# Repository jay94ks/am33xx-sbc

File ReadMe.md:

# AM33xx SBC project.
This project is to create a SBC (Single board computer).
However, despite its name, it is divided into several boards.

## Power-supply board.
  This take power from Type-C USB, and regulates it to 3.3v, 1.8v, 1.5v and 1.1v LDO.
and `STM32G030F6P6` controls power sequence of each voltage lines. And, unfortunately, 
current implementation has no `On/Off` button. when the power cable attached, 
this just turn the board on.

### Rendering:

### Schematic:

### Pinmap.
Pins of the mini power-supply board has following pin map (2.54mm pitch):

```
Right to left order.
1. 1v1
2. 1v5
3. 1v8
4. 3v3
5. 5v
6. SYS_EN
7. USB_DP
8. USB_DM
9. PWRONRSTn
10. WARMRSTn
11. GND
12. GND
```

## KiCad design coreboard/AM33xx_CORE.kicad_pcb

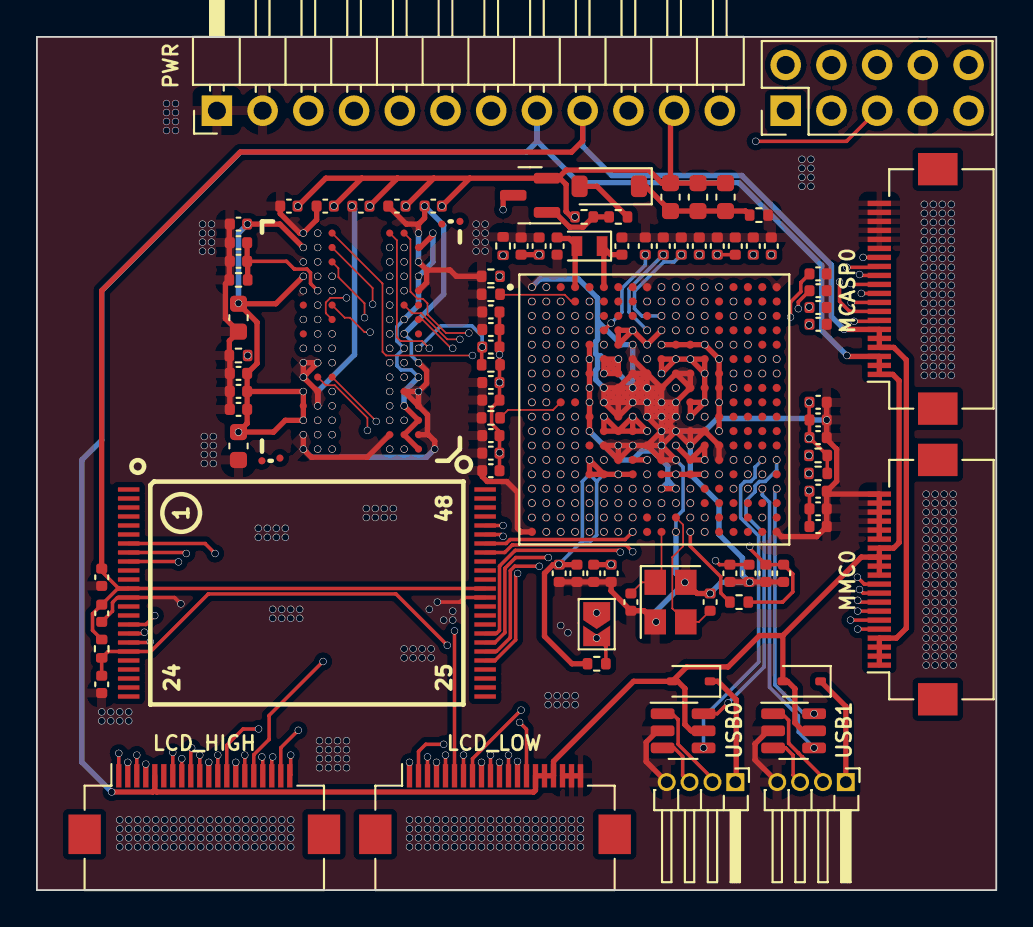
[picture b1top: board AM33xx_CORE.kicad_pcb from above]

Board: 8 copper layers, 53.3 x 47.4 mm, 94 parts (0 on the bottom side), 154 nets.

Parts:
C1, C2, C3, C4, C5, C6, C7, C8, C11, C12, C13, C14, C16, C17, C18, C19, C20, C21, C22, C23, C24, C25, C26, C27, C28, C29, C30, C31, C32, C33, C34, C35, C45, C46, C47, C48, C49, C50, C51, C52, C53, C54, C55, C56, C57, C58: 100nF; C_0402_1005Metric
C9, C10, C59, C60: 10uF; C_0603_1608Metric
C15: 2.2uF; C_0603_1608Metric
C36, C38, C40, C42: 1uF; C_0402_1005Metric
C39, C41: 6.8pF; C_0402_1005Metric
C43, C44: 28pF; C_0402_1005Metric
D1, D3: 1N5819WS; D_SOD-323
D2: 1N4148W; D_SOD-123
J1: PWR; PinHeader_1x12_P2.54mm_Horizontal
J2, J3: Conn_01x04; PinHeader_1x04_P1.27mm_Horizontal
J6: JTAG; PinHeader_2x05_P2.54mm_Vertical
J7: MMC0; Hirose_FH12-20S-0.5SH_1x20-1MP_P0.50mm_Horizontal
J8: LCD_HIGH; Hirose_FH12-20S-0.5SH_1x20-1MP_P0.50mm_Horizontal
J9: LCD_LOW; Hirose_FH12-20S-0.5SH_1x20-1MP_P0.50mm_Horizontal
J10: MCASP0_FPC; Hirose_FH12-20S-0.5SH_1x20-1MP_P0.50mm_Horizontal
JP1: Jumper_2_Open; SolderJumper-2_P1.3mm_Open_TrianglePad1.0x1.5mm
Q1: MMBT3906; SOT-23
R1, R2, R5, R10, R11, R12: 10k; R_0402_1005Metric
R3, R4: 47k; R_0402_1005Metric
R6, R8: 37k; R_0402_1005Metric
R7: 4.7k; R_0402_1005Metric
R9: 47; R_0402_1005Metric
R13, R14: 2k; R_0402_1005Metric
R15: 160k; R_0402_1005Metric
U1, U2: USBLC6-2SC6; SOT-23-6
U3: AM3352BZCZ100; BGA324CP80_18X18_1500X1500X140B50N
U4: H27UBG8T2BTR-BC(TSOP48); TSOP48
U5: H5TQ2G63BFR_MEM4G16D3EABG-125--H5TC8G63AMR-PBA_K4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; FBGA96(HYNIX_SAMSUNG_512MX16_DDR3)
Y1: 32.768kHz; Crystal_SMD_2012-2Pin_2.0x1.2mm
Y2: 24MHz; Crystal_SMD_3225-4Pin_3.2x2.5mm

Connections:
+1.5V: C9.1, C10.1, C15.1, C20.1, C21.1, C24.1, C25.1, C28.1, C29.1, C32.1, C33.1, C48.1, C51.1, C52.1, C53.1, C54.1, C55.1, C56.1, C57.1, C58.1, C59.1, C60.1, J1.11, Q1.2 (E), R3.1, R13.1, U3.D7 (VDDS_RTC), U3.D8 (VDDA_ADC), U3.D10 (VDDS_SRAM_MPU_BB), U3.E5 (VDDS_DDR), U3.E7 (VDDS_PLL_DDR), U3.E9 (VDDS_SRAM_CORE_BG), U3.F5 (VDDS_DDR), U3.G5 (VDDS_DDR), U3.H5 (VDDS_DDR), U3.H15 (VDDS_PLL_MPU), U3.J5 (VDDS_DDR), U3.K5 (VDDS_DDR), U3.L5 (VDDS_DDR), U3.R10 (VDDS_PLL_CORE_LCD), U3.R11 (VDDS_OSC), U5.A1 (VDDQ), U5.A8 (VDDQ), U5.B2 (VDD), U5.C1 (VDDQ), U5.C9 (VDDQ), U5.D2 (VDDQ), U5.D9 (VDD), U5.E9 (VDDQ), U5.F1 (VDDQ), U5.G7 (VDD), U5.H2 (VDDQ), U5.H9 (VDDQ), U5.K2 (VDD), U5.K8 (VDD), U5.N1 (VDD), U5.N9 (VDD), U5.R1 (VDD), U5.R9 (VDD)
+1V1: C1.1, C2.1, C5.1, C6.1, C11.1, C12.1, C16.1, C17.1, J1.12, U3.A2 (VDD_MPU_MON), U3.F6 (VDD_CORE), U3.F7 (VDD_CORE), U3.F10 (VDD_MPU), U3.F11 (VDD_MPU), U3.F12 (VDD_MPU), U3.F13 (VDD_MPU), U3.G6 (VDD_CORE), U3.G7 (VDD_CORE), U3.G10 (VDD_CORE), U3.G13 (VDD_MPU), U3.H11 (VDD_CORE), U3.H13 (VDD_MPU), U3.J12 (VDD_CORE), U3.J13 (VDD_MPU), U3.K6 (VDD_CORE), U3.K8 (VDD_CORE), U3.K12 (VDD_CORE), U3.L6 (VDD_CORE), U3.L7 (VDD_CORE), U3.L8 (VDD_CORE), U3.L9 (VDD_CORE), U3.M11 (VDD_CORE), U3.M13 (VDD_CORE), U3.N8 (VDD_CORE), U3.N9 (VDD_CORE), U3.N12 (VDD_CORE), U3.N13 (VDD_CORE)
+1V8: C3.1, C4.1, C7.1, C8.1, C13.1, C14.1, C18.1, C19.1, J1.10, U3.B9 (VREFP), U3.E6 (VDDS), U3.E14 (VDDS), U3.F9 (VDDS), U3.K13 (VDDS), U3.N6 (VDDS), U3.N16 (VDDA1P8V_USB0), U3.P9 (VDDS), U3.P14 (VDDS), U3.R16 (VDDA1P8V_USB1)
+3V3: C22.1, C23.1, C26.1, C27.1, C30.1, C31.1, C34.1, C35.1, C46.1, C47.1, J1.9, J7.1, J7.2, J7.3, J7.4, J10.4, J10.5, J10.6, R6.1, R8.1, R10.1, R11.2, R12.1, U3.E10 (VDDSHV6), U3.E11 (VDDSHV6), U3.E12 (VDDSHV6), U3.E13 (VDDSHV6), U3.F14 (VDDSHV6), U3.G14 (VDDSHV6), U3.H14 (VDDSHV4), U3.J14 (VDDSHV4), U3.K14 (VDDSHV5), U3.L14 (VDDSHV5), U3.N5 (VDDSHV6), U3.N15 (VDDA3P3V_USB0), U3.P5 (VDDSHV6), U3.P6 (VDDSHV6), U3.P7 (VDDSHV1), U3.P8 (VDDSHV1), U3.P10 (VDDSHV2), U3.P11 (VDDSHV2), U3.P12 (VDDSHV3), U3.P13 (VDDSHV3), U3.R15 (VDDA3P3V_USB1), U4.12 (VCC), U4.37 (VCC)
+5V: D1.2 (A), D3.2 (A), J1.8, J7.11, J7.12, J7.13, J7.14, J8.5, J9.15, J9.16, J9.17, J10.1, J10.2, J10.3, U1.5 (VBUS), U2.5 (VBUS)
/DDR_A0: U3.F3 (DDR_A0), U5.N3 (A0)
/DDR_A1: U3.H1 (DDR_A1), U5.P7 (A1)
/DDR_A2: U3.E4 (DDR_A2), U5.P3 (A2)
/DDR_A3: U3.C3 (DDR_A3), U5.N2 (A3)
/DDR_A4: U3.C2 (DDR_A4), U5.P8 (A4)
/DDR_A5: U3.B1 (DDR_A5), U5.P2 (A5)
/DDR_A6: U3.D5 (DDR_A6), U5.R8 (A6)
/DDR_A7: U3.E2 (DDR_A7), U5.R2 (A7)
/DDR_A8: U3.D4 (DDR_A8), U5.T8 (A8)
/DDR_A9: U3.C1 (DDR_A9), U5.R3 (A9)
/DDR_A10: U3.F4 (DDR_A10), U5.L7 (A10/AP)
/DDR_A11: U3.F2 (DDR_A11), U5.R7 (A11)
/DDR_A12: U3.E3 (DDR_A12), U5.N7 (A12/#BC)
/DDR_A13: U3.H3 (DDR_A13), U5.T3 (A13)
/DDR_A14: U3.H4 (DDR_A14), U5.T7 (NC/A14)
/DDR_A15: U3.D3 (DDR_A15), U5.M7 (NC/A15)
/DDR_BA0: U3.C4 (DDR_BA0), U5.M2 (BA0)
/DDR_BA1: U3.E1 (DDR_BA1), U5.N8 (BA1)
/DDR_BA2: U3.B3 (DDR_BA2), U5.M3 (BA2)
/DDR_CASN: U3.F1 (DDR_CASN), U5.K3 (#CAS)
/DDR_CK: U3.D2 (DDR_CK), U5.J7 (CK)
/DDR_CKE: U3.G3 (DDR_CKE), U5.K9 (CKE)
/DDR_CKN: U3.D1 (DDR_CKN), U5.K7 (#CK)
/DDR_CSN0: U3.H2 (DDR_CSN0), U5.L2 (#CS)
/DDR_D0: U3.M3 (DDR_D0), U5.E3 (DQL0)
/DDR_D1: U3.M4 (DDR_D1), U5.F7 (DQL1)
/DDR_D2: U3.N1 (DDR_D2), U5.F2 (DQL2)
/DDR_D3: U3.N2 (DDR_D3), U5.F8 (DQL3)
/DDR_D4: U3.N3 (DDR_D4), U5.H3 (DQL4)
/DDR_D5: U3.N4 (DDR_D5), U5.H8 (DQL5)
/DDR_D6: U3.P3 (DDR_D6), U5.G2 (DQL6)
/DDR_D7: U3.P4 (DDR_D7), U5.H7 (DQL7)
/DDR_D8: U3.J1 (DDR_D8), U5.D7 (DQU0)
/DDR_D9: U3.K1 (DDR_D9), U5.C3 (DQU1)
/DDR_D10: U3.K2 (DDR_D10), U5.C8 (DQU2)
/DDR_D11: U3.K3 (DDR_D11), U5.C2 (DQU3)
/DDR_D12: U3.K4 (DDR_D12), U5.A7 (DQU4)
/DDR_D13: U3.L3 (DDR_D13), U5.A2 (DQU5)
/DDR_D14: U3.L4 (DDR_D14), U5.B8 (DQU6)
/DDR_D15: U3.M1 (DDR_D15), U5.A3 (DQU7)
/DDR_DQM0: U3.M2 (DDR_DQM0), U5.E7 (DML)
/DDR_DQM1: U3.J2 (DDR_DQM1), U5.D3 (DMU)
/DDR_DQS0: U3.P1 (DDR_DQS0), U5.F3 (DQSL)
/DDR_DQS1: U3.L1 (DDR_DQS1), U5.C7 (DQSU)
/DDR_DQSN0: U3.P2 (DDR_DQSN0), U5.G3 (#DQSL)
/DDR_DQSN1: U3.L2 (DDR_DQSN1), U5.B7 (#DQSU)
/DDR_ODT: U3.G1 (DDR_ODT), U5.K1 (ODT)
/DDR_RASN: U3.G4 (DDR_RASN), U5.J3 (#RAS)
/DDR_RSTN: U3.G2 (DDR_RESETN), U5.T2 (#RESET)
/DDR_WEN: U3.B2 (DDR_WEN), U5.L3 (#WE)
/GMPC_CSN0: JP1.1 (A), U3.V6 (GPMC_CSN0)
/GPMC_AD0: U3.U7 (GPMC_AD0), U4.29 (I/O0)
/GPMC_AD1: U3.V7 (GPMC_AD1), U4.30 (I/O1)
/GPMC_AD2: U3.R8 (GPMC_AD2), U4.31 (I/O2)
/GPMC_AD3: U3.T8 (GPMC_AD3), U4.32 (I/O3)
/GPMC_AD4: U3.U8 (GPMC_AD4), U4.41 (I/O4)
/GPMC_AD5: U3.V8 (GPMC_AD5), U4.42 (I/O5)
/GPMC_AD6: U3.R9 (GPMC_AD6), U4.43 (I/O6)
/GPMC_AD7: U3.T9 (GPMC_AD7), U4.44 (I/O7)
/GPMC_ALE: U3.R7 (GPMC_ADVN_ALE), U4.17 (ALE)
/GPMC_CLE: U3.T6 (GPMC_BEN0_CLE), U4.16 (CLE)
/GPMC_CLK: R12.2, U3.V12 (GPMC_CLK), U4.7 (RB1#)
/GPMC_REN: U3.T7 (GPMC_OEN_REN), U4.8 (#RE)
/GPMC_WEN: U3.U6 (GPMC_WEN), U4.18 (#WE)
/GPMC_WPN: C45.1, R10.2, U3.U17 (GPMC_WPN), U4.19 (#WP)
/LCD_D0/R3: J8.11, U3.R1 (LCD_DATA0)
/LCD_D1/R4: J8.12, U3.R2 (LCD_DATA1)
/LCD_D2/R5: J8.14, U3.R3 (LCD_DATA2)
/LCD_D3/R6: J9.14, U3.R4 (LCD_DATA3)
/LCD_D4/R7: J8.13, U3.T1 (LCD_DATA4)
/LCD_D5/G2: J8.17, U3.T2 (LCD_DATA5)
/LCD_D6/G3: J8.20, U3.T3 (LCD_DATA6)
/LCD_D7/G4: J9.1, U3.T4 (LCD_DATA7)
/LCD_D8/G5: J9.2, U3.U1 (LCD_DATA8)
/LCD_D9/G6: J8.18, U3.U2 (LCD_DATA9)
/LCD_D10/G7: J8.19, U3.U3 (LCD_DATA10)
/LCD_D11/B3: J9.8, U3.U4 (LCD_DATA11)
/LCD_D12/B4: J9.9, U3.V2 (LCD_DATA12)
/LCD_D13/B5: J9.10, U3.V3 (LCD_DATA13)
/LCD_D14/B6: J9.4, U3.V4 (LCD_DATA14)
/LCD_D15/B7: J9.5, U3.T5 (LCD_DATA15)
/LCD_D16/R2: J8.10, U3.U13 (GPMC_AD15)
/LCD_D17/B2: J9.7, U3.V13 (GPMC_AD14)
/LCD_D18/R1: J8.9, U3.R12 (GPMC_AD13)
/LCD_D19/G1: J8.16, U3.T12 (GPMC_AD12)
/LCD_D20/B1: J9.6, U3.U12 (GPMC_AD11)
/LCD_D21/R0: J8.8, U3.T11 (GPMC_AD10)
/LCD_D22/G0: J8.15, U3.T10 (GPMC_AD9)
/LCD_D23/B0: J9.3, U3.U10 (GPMC_AD8)
/LCD_D24/HSYNC: J9.11, U3.R5 (LCD_HSYNC)
/LCD_D25/VSYNC: J9.12, U3.U5 (LCD_VSYNC)
/LCD_D26/ENABLE: J9.13, U3.R6 (LCD_AC_BIAS_EN)
/LCD_D27/PCLK: J8.7, U3.V5 (LCD_PCLK)
/USB_RAW_DM0: J2.2, U1.1 (I/O1)
/USB_RAW_DM1: J3.2, U2.1 (I/O1)
/USB_RAW_DP0: J2.3, U1.3 (I/O2)
/USB_RAW_DP1: J3.3, U2.3 (I/O2)
EDID_SCL: J8.3, U3.C16 (I2C0_SCL)
EDID_SDA: J8.4, U3.C17 (I2C0_SDA)
GND: C1.2, C2.2, C3.2, C4.2, C5.2, C6.2, C7.2, C8.2, C11.2, C12.2, C13.2, C14.2, C16.2, C17.2, C18.2, C19.2, C20.2, C21.2, C22.2, C23.2, C24.2, C25.2, C26.2, C27.2, C28.2, C29.2, C30.2, C31.2, C32.2, C33.2, C34.2, C35.2, C36.2, C38.2, C39.1, C40.2, C41.1, C42.2, C43.1, C44.1, C45.2, C46.2, C47.2, C49.2, C50.2, C51.2, C52.2, C53.2, C54.2, C55.2, C56.2, C57.2, C58.2, C59.2, C60.2, J1.1, J1.2, J2.4, J3.4, J6.7, J6.8, J7.15, J7.16, J7.17, J7.18, J7.19, J7.20, J8.6, J9.18, J9.19, J9.20, J10.15, J10.16, J10.17, J10.18, J10.19, J10.20, R1.2, R4.2, R5.2, R7.2, R9.1, R14.2, R15.2, U1.2 (GND), U2.2 (GND), U3.A1 (VSS), U3.A5 (VSS_RTC), U3.A9 (VREFN), U3.A18 (VSS), U3.E8 (VSSA_ADC), U3.F8 (VSS), U3.G8 (VSS), U3.G9 (VSS), U3.G11 (VSS), U3.G12 (VSS), U3.H6 (VSS), U3.H7 (VSS), U3.H8 (VSS), U3.H9 (VSS), U3.H10 (VSS), U3.H12 (VSS), U3.J6 (VSS), U3.J7 (VSS), U3.J8 (VSS), U3.J9 (VSS), U3.J10 (VSS), U3.J11 (VSS), U3.K7 (VSS), U3.K9 (VSS), U3.K10 (VSS), U3.K11 (VSS), U3.L10 (VSS), U3.L11 (VSS), U3.L12 (VSS), U3.L13 (VSS), U3.M6 (VSS), U3.M7 (VSS), U3.M8 (VSS), U3.M9 (VSS), U3.M10 (VSS), U3.M12 (VSS), U3.M14 (VSSA_USB), U3.N7 (VSS), U3.N10 (VSS), U3.N11 (VSS), U3.N14 (VSSA_USB), U3.V1 (VSS), U3.V11 (VSS_OSC), U3.V18 (VSS), U4.13 (VSS), U4.36 (VSS), U5.A9 (VSS), U5.B1 (VSSQ), U5.B3 (VSS), U5.B9 (VSSQ), U5.D1 (VSSQ), U5.D8 (VSSQ), U5.E1 (VSS), U5.E2 (VSSQ), U5.E8 (VSSQ), U5.F9 (VSSQ), U5.G1 (VSSQ), U5.G8 (VSS), U5.G9 (VSSQ), U5.J2 (VSS), U5.J8 (VSS), U5.M1 (VSS), U5.M9 (VSS), U5.P1 (VSS), U5.P9 (VSS), U5.T1 (VSS), U5.T9 (VSS), Y2.2, Y2.4
MCASP0_ACLKR: J10.8, U3.B12 (MCASP0_ACLKR)
MCASP0_ACLKX: J10.11, U3.A13 (MCASP0_ACLKX)
MCASP0_AHCLKR: J10.9, U3.C12 (MCASP0_AHCLKR)
MCASP0_AHCLKX: J10.10, U3.A14 (MCASP0_AHCLKX)
MCASP0_AXR0: J10.13, U3.D12 (MCASP0_AXR0)
MCASP0_AXR1: J10.14, U3.D13 (MCASP0_AXR1)
MCASP0_FSR: J10.12, U3.C13 (MCASP0_FSR)
MCASP0_FSX: J10.7, U3.B13 (MCASP0_FSX)
MMC0_CLK: J7.6, U3.G17 (MMC0_CLK)
MMC0_CMD: J7.5, U3.G18 (MMC0_CMD)
MMC0_DAT0: J7.7, U3.G16 (MMC0_DAT0)
MMC0_DAT1: J7.8, U3.G15 (MMC0_DAT1)
MMC0_DAT2: J7.9, U3.F18 (MMC0_DAT2)
MMC0_DAT3: J7.10, U3.F17 (MMC0_DAT3)
unnamed: D1.1 (K), J2.1
unnamed: D2.2 (A), R2.1
unnamed: C9.2, C10.2, C15.2, D2.1 (K), R1.1
unnamed: D3.1 (K), J3.1
unnamed: JP1.2 (B), R11.1, U4.9 (CE1#)
unnamed: Q1.1 (B), R2.2, R3.2
unnamed: C36.1, U3.C10 (CAP_VBB_MPU)
unnamed: C42.1, U3.D6 (CAP_VDD_RTC)
unnamed: C40.1, U3.D9 (CAP_VDD_SRAM_CORE)
unnamed: C38.1, U3.D11 (CAP_VDD_SRAM_MPU)
unnamed: R9.2, U3.J3 (DDR_VTP)
unnamed: R7.1, U3.C5 (EXT_WAKEUP)
unnamed: R5.1, U3.B4 (RTC_KALDO_ENN)
unnamed: C41.2, U3.A4 (RTC_XTALOUT), Y1.2
unnamed: R8.2, U3.P16 (USB0_ID)
unnamed: R6.2, U3.P17 (USB1_ID)
unnamed: C44.2, U3.U11 (XTALOUT), Y2.3
unnamed: C48.2, C49.1, C50.1, R13.2, R14.1, U5.H1 (VREFDQ), U5.M8 (VREFCA)
unnamed: R15.1, U5.L8 (ZQ)
PWR_PWRONRSTn: J1.4, U3.B15 (PWRONRSTN)
PWR_WARMRSTn: J1.3, U3.A10 (WARMRSTN)
RTC_PORZ: Q1.3 (C), R4.1, U3.B5 (RTC_PWRONRSTN)
RTC_XTAL_IN: C39.2, U3.A6 (RTC_XTALIN), Y1.1
TCK: J6.4, U3.A12 (TCK)
TDI: J6.2, U3.B11 (TDI)
TDO: J6.1, U3.A11 (TDO)
TMS: J6.3, U3.C11 (TMS)
TRST: J6.5, U3.B10 (~TRSTN)
UART0_RXD: J8.1, U3.E15 (UART0_RXD)
UART0_TXD: J8.2, U3.E16 (UART0_TXD)
USB0_DM: U1.6 (I/O1), U3.N18 (USB0_DM)
USB0_DP: U1.4 (I/O2), U3.N17 (USB0_DP)
USB1_DM: U2.6 (I/O1), U3.R18 (USB1_DM)
USB1_DP: U2.4 (I/O2), U3.R17 (USB1_DP)
XTAL_IN: C43.2, U3.V10 (XTALIN), Y2.1

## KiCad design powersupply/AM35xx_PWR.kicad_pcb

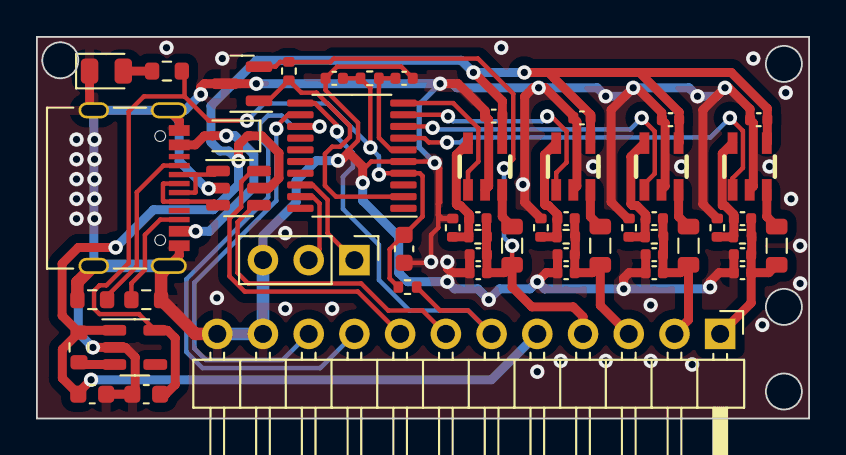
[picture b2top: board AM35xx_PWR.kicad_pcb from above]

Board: 2 copper layers, 42.9 x 21.2 mm, 53 parts (0 on the bottom side), 35 nets.

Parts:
C2, C3, C6, C7, C8, C9, C10, C11, C15, C16, C17, C18: 22uF; C_0402_1005Metric
C4, C5, C12, C13: 22pF; C_0402_1005Metric
C14, C19: 10uF; C_0603_1608Metric
C20, C21: 100nF; C_0402_1005Metric
C22: 4.7uF; C_0603_1608Metric
D1: 1N5819WS; D_SOD-323
D2: LED/G; LED_0805_2012Metric
J1: USB_C_Receptacle_USB2.0; USB_C_Receptacle_Palconn_UTC16-G
J2: MPU; PinHeader_1x12_P2.54mm_Horizontal
J3: SWD; PinHeader_1x03_P2.54mm_Vertical
L1, L2, L3, L4: 2.2uH; L_0805_2012Metric
R2, R3: 5.1k; R_0603_1608Metric
R4, R7: 1k; R_0402_1005Metric
R5: 1.2k; R_0402_1005Metric
R6: 2k; R_0402_1005Metric
R10, R12: 4.99k; R_0402_1005Metric
R11: 3.3k; R_0402_1005Metric
R13: 1.1k; R_0402_1005Metric
R14: 100k; R_0603_1608Metric
R15: 1k; R_0603_1608Metric
R16, R17, R18: 10k; R_0402_1005Metric
U1, U2, U4, U5: SY8009AAAC(SOT23-5); SOT-23-5
U3: USBLC6-2SC6; SOT-23-6
U6: XC6220B331MR; SOT-23-5
U7: MCP130-300LITT; SOT-23
U8: STM32G030F6Px; TSSOP-20_4.4x6.5mm_P0.65mm

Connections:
1V1_EN: U1.1 (EN), U8.7 (PA0)
1V5_EN: U4.1 (EN), U8.8 (PA1)
1V8_EN: U2.1 (EN), U8.9 (PA2)
3V3_EN: U5.1 (EN), U8.10 (PA3)
+1.5V: C12.1, C15.1, C17.1, J2.2, L3.2, R10.1
+1V1: C4.1, C6.1, C8.1, J2.1, L1.2, R4.1
+1V8: C5.1, C7.1, C9.1, J2.3, L2.2, R6.1
+3V3: C13.1, C16.1, C18.1, J2.4, L4.2, R12.1, R17.2, U7.2 (VDD)
+5V: C2.1, C3.1, C10.1, C11.1, C14.1, D1.1 (K), J2.5, R14.2, U1.4 (IN), U2.4 (IN), U3.5 (VBUS), U4.4 (IN), U5.4 (IN), U6.1 (VIN)
/USB_RAW_DM: J1.A7 (D-), J1.B7 (D-), U3.1 (I/O1)
/USB_RAW_DP: J1.A6 (D+), J1.B6 (D+), U3.3 (I/O2)
GND: C2.2, C3.2, C6.2, C7.2, C8.2, C9.2, C10.2, C11.2, C14.2, C15.2, C16.2, C17.2, C18.2, C19.2, C20.2, C21.2, C22.1, D2.1 (K), J1.A1 (GND), J1.A12 (GND), J1.B1 (GND), J1.B12 (GND), J1.S1 (SHIELD), J2.11, J2.12, J3.3, R2.2, R3.2, R5.2, R7.2, R11.2, R13.2, U1.2 (GND), U2.2 (GND), U3.2 (GND), U4.2 (GND), U5.2 (GND), U6.2 (GND), U7.3 (VSS), U8.5 (VSS)
MCP130: R17.1, U7.1 (~RST), U8.2 (PC14/PB9)
unnamed: D1.2 (A), J1.A4 (VBUS), J1.A9 (VBUS), J1.B4 (VBUS), J1.B9 (VBUS)
unnamed: D2.2 (A), R15.1
unnamed: J1.A5 (CC1), R2.1
unnamed: J1.B5 (CC2), R3.1
unnamed: C4.2, R4.2, R5.1, U1.5 (FB)
unnamed: L1.1, U1.3 (LX)
unnamed: C5.2, R6.2, R7.1, U2.5 (FB)
unnamed: L2.1, U2.3 (LX)
unnamed: C12.2, R10.2, R11.1, U4.5 (FB)
unnamed: L3.1, U4.3 (LX)
unnamed: C13.2, R12.2, R13.1, U5.5 (FB)
unnamed: L4.1, U5.3 (LX)
unnamed: R14.1, U6.3 (CE)
unnamed: C20.1, R16.1, U8.6 (NRST)
PWRONRSTn: J2.9, U8.13 (PA6)
SWCLK: J3.2, U8.19 (PA14/PA15)
SWDIO: J3.1, U8.18 (PA13)
SYS_EN: J2.6, R18.1, U8.11 (PA4)
USB_DM: J2.8, U3.6 (I/O1)
USB_DP: J2.7, U3.4 (I/O2)
VCC: C19.1, C21.1, C22.2, R15.2, R16.2, R18.2, U6.5 (VOUT), U8.4 (VDD)
WARMRSTn: J2.10, U8.12 (PA5)

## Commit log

2024-03-29 Initial commit.
2024-03-30 Core board
